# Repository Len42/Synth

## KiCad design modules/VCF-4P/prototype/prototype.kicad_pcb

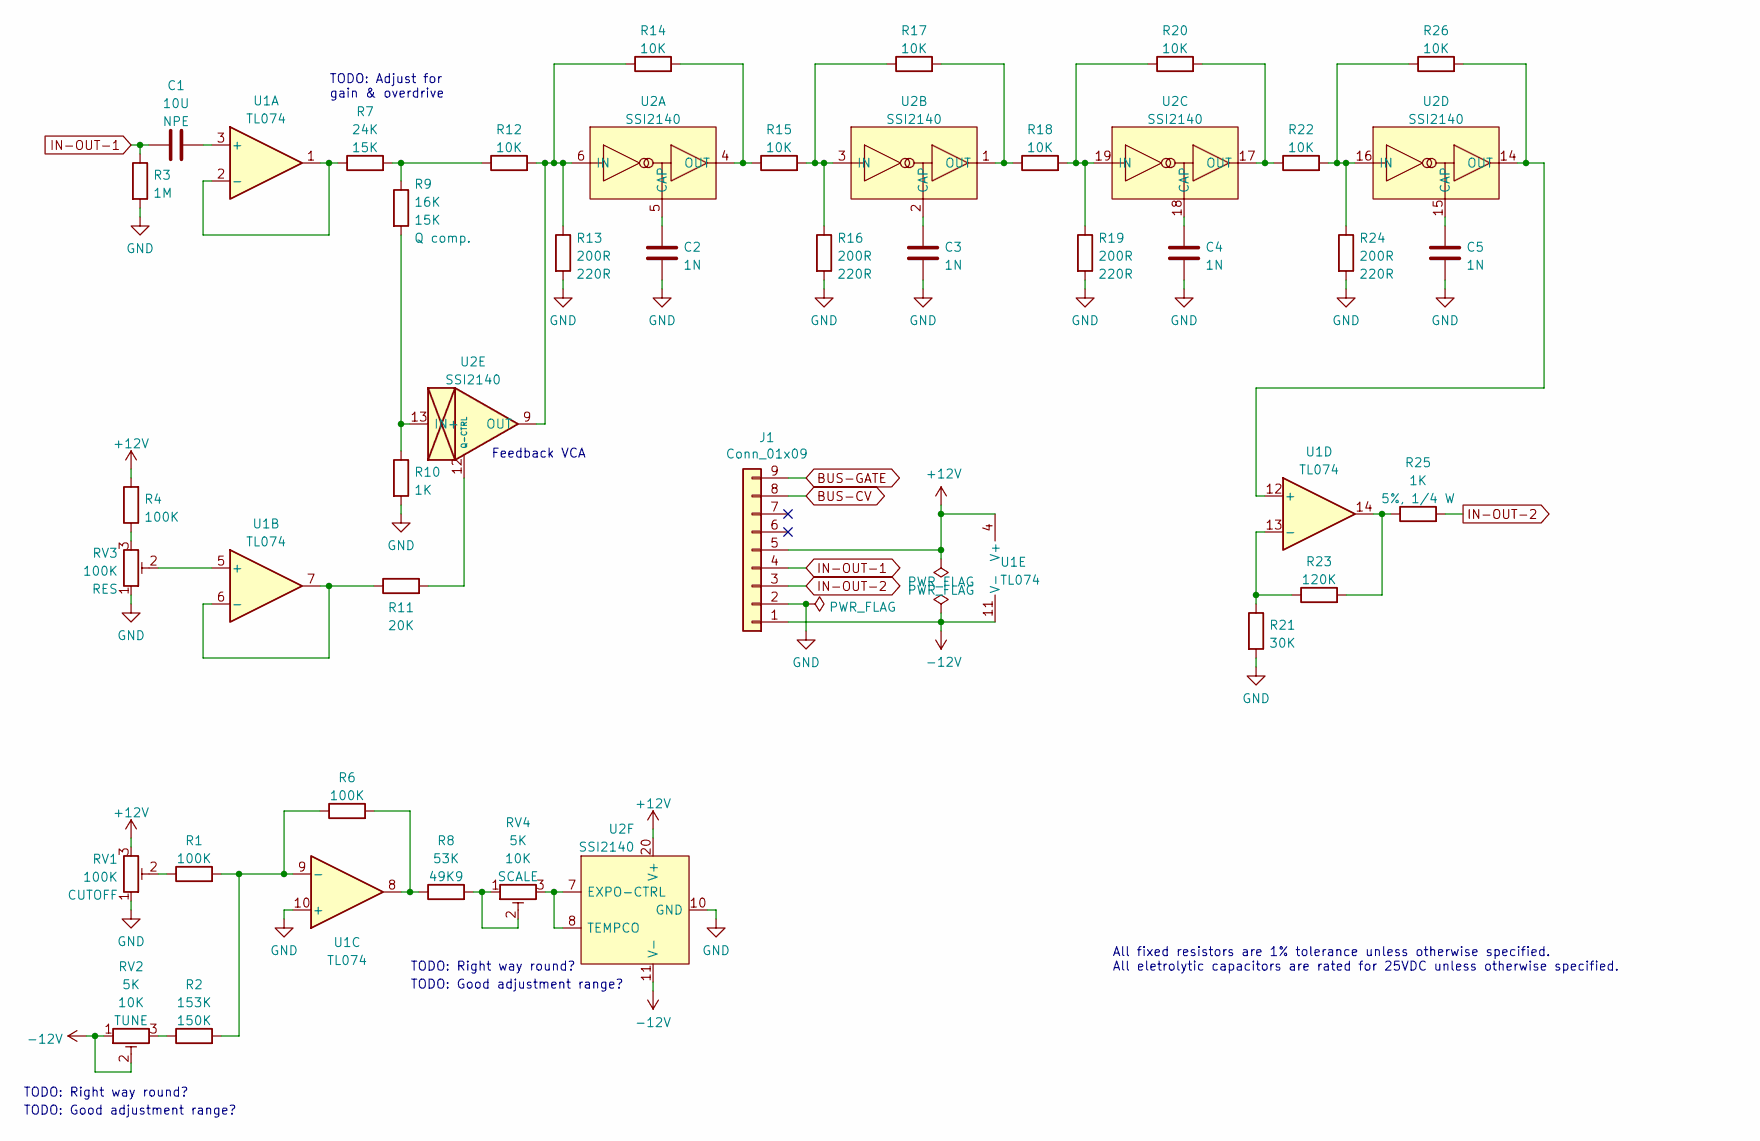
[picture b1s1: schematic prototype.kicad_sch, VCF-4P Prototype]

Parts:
C1: 10U; C_Radial_D5.0mm_H5.0mm_P2.50mm; ManufacturerPartNum ECE-A1EN100UI
C2, C3, C4, C5: 1N; C_Rect_Kemet_L7.2mm_W2.5mm_P5mm
J1: Conn_01x09; PinHeader_1x09_P2.54mm_Vertical
R1: 100K; R_Axial_DIN0207_L6.3mm_D2.5mm_P7.62mm_Horizontal; ManufacturerPartNum MFR-12*
R2: 153K; R_Axial_DIN0207_L6.3mm_D2.5mm_P7.62mm_Horizontal; ManufacturerPartNum MFR-12*
R3: 1M; SB_Gen_1; ManufacturerPartNum MFR-12*
R4: 100K; SB_Gen_2; ManufacturerPartNum MFR-12*
R6: 100K; SB_Gen_1; ManufacturerPartNum MFR-12*
R7: 24K; R_Axial_DIN0207_L6.3mm_D2.5mm_P7.62mm_Horizontal; ManufacturerPartNum MFR-12*
R8: 53K; R_Axial_DIN0207_L6.3mm_D2.5mm_P7.62mm_Horizontal; ManufacturerPartNum MFR-12*
R9: 16K; R_Axial_DIN0207_L6.3mm_D2.5mm_P7.62mm_Horizontal; ManufacturerPartNum MFR-12*
R10: 1K; SB_Gen_1; ManufacturerPartNum MFR-12*
R11: 20K; SB_Gen_1; ManufacturerPartNum MFR-12*
R12, R18: 10K; R_Axial_DIN0207_L6.3mm_D2.5mm_P7.62mm_Horizontal; ManufacturerPartNum MFR-12*
R13, R16, R19, R24: 200R; SB_Gen_1; ManufacturerPartNum MFR-12*
R14, R17, R20, R26: 10K; SB_Gen_2; ManufacturerPartNum MFR-12*
R15, R22: 10K; SB_Gen_1; ManufacturerPartNum MFR-12*
R21: 30K; R_Axial_DIN0207_L6.3mm_D2.5mm_P7.62mm_Horizontal; ManufacturerPartNum MFR-12*
R23: 120K; SB_Gen_1; ManufacturerPartNum MFR-12*
R25: 1K; SB_Gen_2; ManufacturerPartNum CCF071K00JKE36
RV1, RV3: 100K; Potentiometer_Bourns_3310R_Top; ManufacturerPartNum 3386*
RV2, RV4: 5K; Potentiometer_Bourns_3310R_Top; ManufacturerPartNum 3386*
U1: TL074; DIP-14_W7.62mm; ManufacturerPartNum TL074BCN
U2: SSI2140; Breakout_DIP-20_W15.24mm; ManufacturerPartNum SSI2140

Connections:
+12V: J1.5, R4.2, RV1.3, U1.4 (V+), U2.20 (V+)
-12V: J1.1, RV2.1, RV2.2, U1.11 (V-), U2.11 (V-)
BUS-CV: J1.8
BUS-GATE: J1.9
GND: C2.2, C3.2, C4.2, C5.2, J1.2, R3.2, R10.2, R13.2, R16.2, R19.2, R21.2, R24.2, RV1.1, RV3.1, U1.10 (+), U2.10 (GND)
IN-OUT-1: C1.1, J1.4, R3.1
IN-OUT-2: J1.3, R25.2
unnamed: C1.2, U1.3 (+)
unnamed: C2.1, U2.5 (CAP)
unnamed: C3.1, U2.2 (CAP)
unnamed: C4.1, U2.18 (CAP)
unnamed: C5.1, U2.15 (CAP)
unnamed: R1.1, RV1.2
unnamed: R1.2, R2.2, R6.1, U1.9 (-)
unnamed: R2.1, RV2.3
unnamed: R4.1, RV3.3
unnamed: R6.2, R8.1, U1.8
unnamed: R7.1, U1.1, U1.2 (-)
unnamed: R8.2, RV4.1, RV4.2
unnamed: R9.2, R10.1, U2.13 (IN+)
unnamed: R11.1, U1.6 (-), U1.7
unnamed: R11.2, U2.12 (Q-CTRL)
unnamed: R7.2, R9.1, R12.1
unnamed: R12.2, R13.1, R14.1, U2.6 (IN), U2.9 (OUT)
unnamed: R14.2, R15.1, U2.4 (OUT)
unnamed: R15.2, R16.1, R17.1, U2.3 (IN)
unnamed: R17.2, R18.1, U2.1 (OUT)
unnamed: R18.2, R19.1, R20.1, U2.19 (IN)
unnamed: R20.2, R22.1, U2.17 (OUT)
unnamed: R21.1, R23.1, U1.13 (-)
unnamed: R22.2, R24.1, R26.1, U2.16 (IN)
unnamed: R23.2, R25.1, U1.14
unnamed: R26.2, U1.12 (+), U2.14 (OUT)
unnamed: RV3.2, U1.5 (+)
unnamed: RV4.3, U2.7 (EXPO-CTRL), U2.8 (TEMPCO)

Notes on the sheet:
TODO: Good adjustment range?
TODO: Right way round?
TODO: Adjust for gain & overdrive
All fixed resistors are 1% tolerance unless otherwise specified. All eletrolytic capacitors are rated for 25VDC unless otherwise specified.
Feedback VCA

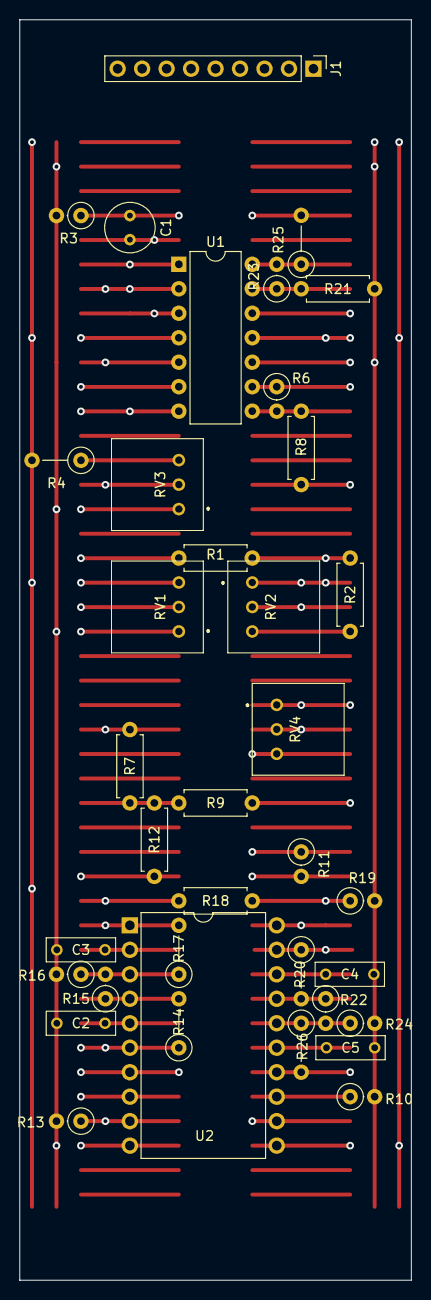
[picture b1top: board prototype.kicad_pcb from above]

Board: 6 copper layers, 40.6 x 130.8 mm, 37 parts (0 on the bottom side), 33 nets.

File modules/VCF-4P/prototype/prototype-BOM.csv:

Ref,Qty,Value,Value2,Note,Description,Datasheet,Manufacturer,ManuPartNum,Distributor1,DistributorPartNum1,DistributorPartLink1,Distributor2,DistributorPartNum2,DistributorPartLink2,Distributor3,DistributorPartNum3,DistributorPartLink3
"C1","1","10U","NPE","","Capacitor - Non-polarized Electrolytic","https://www.mouser.ca/datasheet/2/315/ABA0000C1053-947510.pdf","Panasonic","ECE-A1EN100UI","Mouser","667-ECE-A1EN100UI","https://www.mouser.ca/ProductDetail/Panasonic/ECE-A1EN100UI?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","","","","","",""
"C2 C3 C4 C5","4","1N","","","Capacitor - Film","","","","","","","","","","","",""
"J1","1","Conn_01x09","","","Generic connector, single row, 01x09, script generated (kicad-library-utils/schlib/autogen/connector/)","","","","","","","","","","","",""
"R1 R21","2","120K","1%, 1/6 W","","Resistor","https://www.mouser.ca/datasheet/2/447/Yageo_LR_MFR_1-1714151.pdf","YAGEO","MFR-12*","Mouser","603-MFR-12*","https://www.mouser.ca/c/?m=YAGEO&power+rating=166+mW+(1%2f6+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","","","","","",""
"R2","1","153K","150K","","Resistor","https://www.mouser.ca/datasheet/2/447/Yageo_LR_MFR_1-1714151.pdf","YAGEO","MFR-12*","Mouser","603-MFR-12*","https://www.mouser.ca/c/?m=YAGEO&power+rating=166+mW+(1%2f6+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","","","","","",""
"R3","1","1M","1%, 1/6 W","","Resistor","https://www.mouser.ca/datasheet/2/447/Yageo_LR_MFR_1-1714151.pdf","YAGEO","MFR-12*","Mouser","603-MFR-12*","https://www.mouser.ca/c/?m=YAGEO&power+rating=166+mW+(1%2f6+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","","","","","",""
"R4 R5 R6","3","100K","1%, 1/6 W","","Resistor","https://www.mouser.ca/datasheet/2/447/Yageo_LR_MFR_1-1714151.pdf","YAGEO","MFR-12*","Mouser","603-MFR-12*","https://www.mouser.ca/c/?m=YAGEO&power+rating=166+mW+(1%2f6+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","","","","","",""
"R7","1","24K","15K","","Resistor","https://www.mouser.ca/datasheet/2/447/Yageo_LR_MFR_1-1714151.pdf","YAGEO","MFR-12*","Mouser","603-MFR-12*","https://www.mouser.ca/c/?m=YAGEO&power+rating=166+mW+(1%2f6+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","","","","","",""
"R8","1","53K","49K9","","Resistor","https://www.mouser.ca/datasheet/2/447/Yageo_LR_MFR_1-1714151.pdf","YAGEO","MFR-12*","Mouser","603-MFR-12*","https://www.mouser.ca/c/?m=YAGEO&power+rating=166+mW+(1%2f6+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","","","","","",""
"R9","1","16K","15K","Q comp.","Resistor","https://www.mouser.ca/datasheet/2/447/Yageo_LR_MFR_1-1714151.pdf","YAGEO","MFR-12*","Mouser","603-MFR-12*","https://www.mouser.ca/c/?m=YAGEO&power+rating=166+mW+(1%2f6+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","","","","","",""
"R10","1","1K","1%, 1/6 W","","Resistor","https://www.mouser.ca/datasheet/2/447/Yageo_LR_MFR_1-1714151.pdf","YAGEO","MFR-12*","Mouser","603-MFR-12*","https://www.mouser.ca/c/?m=YAGEO&power+rating=166+mW+(1%2f6+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","","","","","",""
"R11","1","20K","1%, 1/6 W","","Resistor","https://www.mouser.ca/datasheet/2/447/Yageo_LR_MFR_1-1714151.pdf","YAGEO","MFR-12*","Mouser","603-MFR-12*","https://www.mouser.ca/c/?m=YAGEO&power+rating=166+mW+(1%2f6+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","","","","","",""
"R12 R14 R15 R17 R18 R20 R22 R26","8","10K","1%, 1/6 W","","Resistor","https://www.mouser.ca/datasheet/2/447/Yageo_LR_MFR_1-1714151.pdf","YAGEO","MFR-12*","Mouser","603-MFR-12*","https://www.mouser.ca/c/?m=YAGEO&power+rating=166+mW+(1%2f6+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","","","","","",""
"R13 R16 R19 R24","4","200R","220R","","Resistor","https://www.mouser.ca/datasheet/2/447/Yageo_LR_MFR_1-1714151.pdf","YAGEO","MFR-12*","Mouser","603-MFR-12*","https://www.mouser.ca/c/?m=YAGEO&power+rating=166+mW+(1%2f6+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","","","","","",""
"R23","1","30K","1%, 1/6 W","","Resistor","https://www.mouser.ca/datasheet/2/447/Yageo_LR_MFR_1-1714151.pdf","YAGEO","MFR-12*","Mouser","603-MFR-12*","https://www.mouser.ca/c/?m=YAGEO&power+rating=166+mW+(1%2f6+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","","","","","",""
"R25","1","1K","5%, 1/4 W","Output limiting","Resistor","https://www.mouser.ca/datasheet/2/427/ccf07-1762725.pdf","Vishay / Dale","CCF071K00JKE36","Mouser","71-CCF071K00JKE36","https://www.mouser.ca/ProductDetail/Vishay-Dale/CCF071K00JKE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","","","","","",""
"RV1 RV3","2","100K","","","Trim-potentiometer","https://www.mouser.ca/datasheet/2/54/3386-776606.pdf","Bourns","3386*","Mouser","652-3386*","https://www.mouser.ca/c/passive-components/resistors/variabl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","","","","","",""
"RV2 RV4","2","5K","10K","","Trim-potentiometer","https://www.mouser.ca/datasheet/2/54/3386-776606.pdf","Bourns","3386*","Mouser","652-3386*","https://www.mouser.ca/c/passive-components/resistors/variabl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","","","","","",""
"U1","1","TL074","","","Quad Low-Noise JFET-Input Operational Amplifiers, DIP-14/SOIC-14","http://www.ti.com/lit/ds/symlink/tl071.pdf","Texas Instruments","TL074BCN","Mouser","595-TL074BCN","https://www.mouser.ca/ProductDetail/?qs=vxEfx8VrU7BHurOY5iQd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","","","","","",""
"U2","1","SSI2140","","","Voltage Controlled Filter (VCF), SSOP-20","http://soundsemiconductor.com/downloads/ssi2140datasheet.pdf","Sound Semiconductor","SSI2140","Antique Electronic Supply","P-Q-SSI2140","https://www.tubesandmore.com/products/integrated-circuit-ssi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","SynthCube","ICSMSSI2140","https://synthcube.com/cart/ics-and-semiconductors/sound-semi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","Thonk","SSI2140","https://www.thonk.co.uk/shop/sound-semiconductor/"

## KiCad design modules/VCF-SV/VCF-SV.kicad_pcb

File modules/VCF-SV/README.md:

# State-Variable VCF

## 10HP Eurorack Module

_A state-variable filter using the CEM3320 chip_

### Features
- Two-pole state-variable filter made with a [CEM3320 IC](https://electricdruid.net/wp-content/uploads/2017/06/CEM3320-VCF.pdf)
- Two separate outputs:
    - Continuously-variable low-pass - notch - high-pass filter response
    - Bandpass filter
- Self-oscillates at maximum resonance
- Two CV inputs for cutoff/centre frequency. One is 1V/octave and the other has an input attenuator.
- 1V/octave input can default to the Eurorack bus CV line (jumper-selectable) - more info [here](https://lenp.net/synth/eurorack-bus-cv-gate.html)
- Resonance CV input with attenuator

### Notes
The cutoff CV inputs can be trimmed to track 1V/octave pretty well (but not as accurately as a VCO). The temperature-compensation resistor, RT1, should be mounted in thermal contact with the CEM3320 chip (see photo).

This module requires a 16-pin Eurorack power cable, but it does not depend on +5V power from the Eurorack system.

### Calibration
There are three trimmer potentiometers on the back of the module that should be adjusted for best results.

First, adjust the "DC TRIM" trimmer (RV8) to minimize control voltage feedthrough.
- Disconnect all inputs from the module.
- Set the cutoff and resonance controls fully counter-clockwise.
- Connect an audio signal (e.g. from a VCO) to the module's volt-per-octave CV input.
- Connect either of the the module's outputsj to an oscilloscope, or just listen to it.
- Adjust RV8 for the minimum output signal.

Then adjust RV6 (TUNE) and RV7 (SCALE) so the cutoff/centre frequency responds accurately to the volt-per-octave CV input. If you care.
- Disconnect the module's audio input.
- Connect a keyboard or other pitch CV source to the module's the 1V/octave CV input.
- Turn the resonance control fully clockwise. This will cause the filter to oscillate.
- Connect either of the the module's outputs to a tuner or frequency counter.
- Adjust RV6 & RV7 while playing different notes until the output is in tune (more or less) across several octaves.

Don't expect the tuning to be as accurate or as stable as a VCO.

If you don't care about precise volt/octave scaling, you can just set the trim pots RV6 & RV7 somewhere near the middle, or even replace them with fixed resistors (13 kΩ and 4.7 kΩ respectively). Also, you may replace tempco resistor RT1 with an ordinary resistor (1% metal film preferred).

### PCBs
PCB layouts are provided in KiCad and gerber formats. A PCB layout for a drilled front panel (with no labels) is also included.

The PCBs that I used can be ordered from OSH Park. The designs are here:
- [Front panel](https://oshpark.com/shared_projects/KgoN3yfz)
- [Controls board](https://oshpark.com/shared_projects/U095EDGt)
- [Main board](https://oshpark.com/shared_projects/O1sdHBEZ)

Please note that I am a hobbyist, not a trained electronics engineer. No guarantees!

### Acknowledgements

This design is based in part on the [Tellun TLN-428 module by Scott Juskiw](http://www.tellun.com/motm/diy/tln428/TLN-428.html).

### Software Used

* [KiCad](https://www.kicad.org/) 6.0.9

<hr /><div><div style="float:left; padding-right:10px;"></div><div style="xfloat:left; padding-left:10px;"><br />© 2022 Len Popp CC BY<br />This work is licensed under a <a rel="license" href="http://creativecommons.org/licenses/by/4.0/">Creative Commons Attribution 4.0 International License</a>.</div></div>

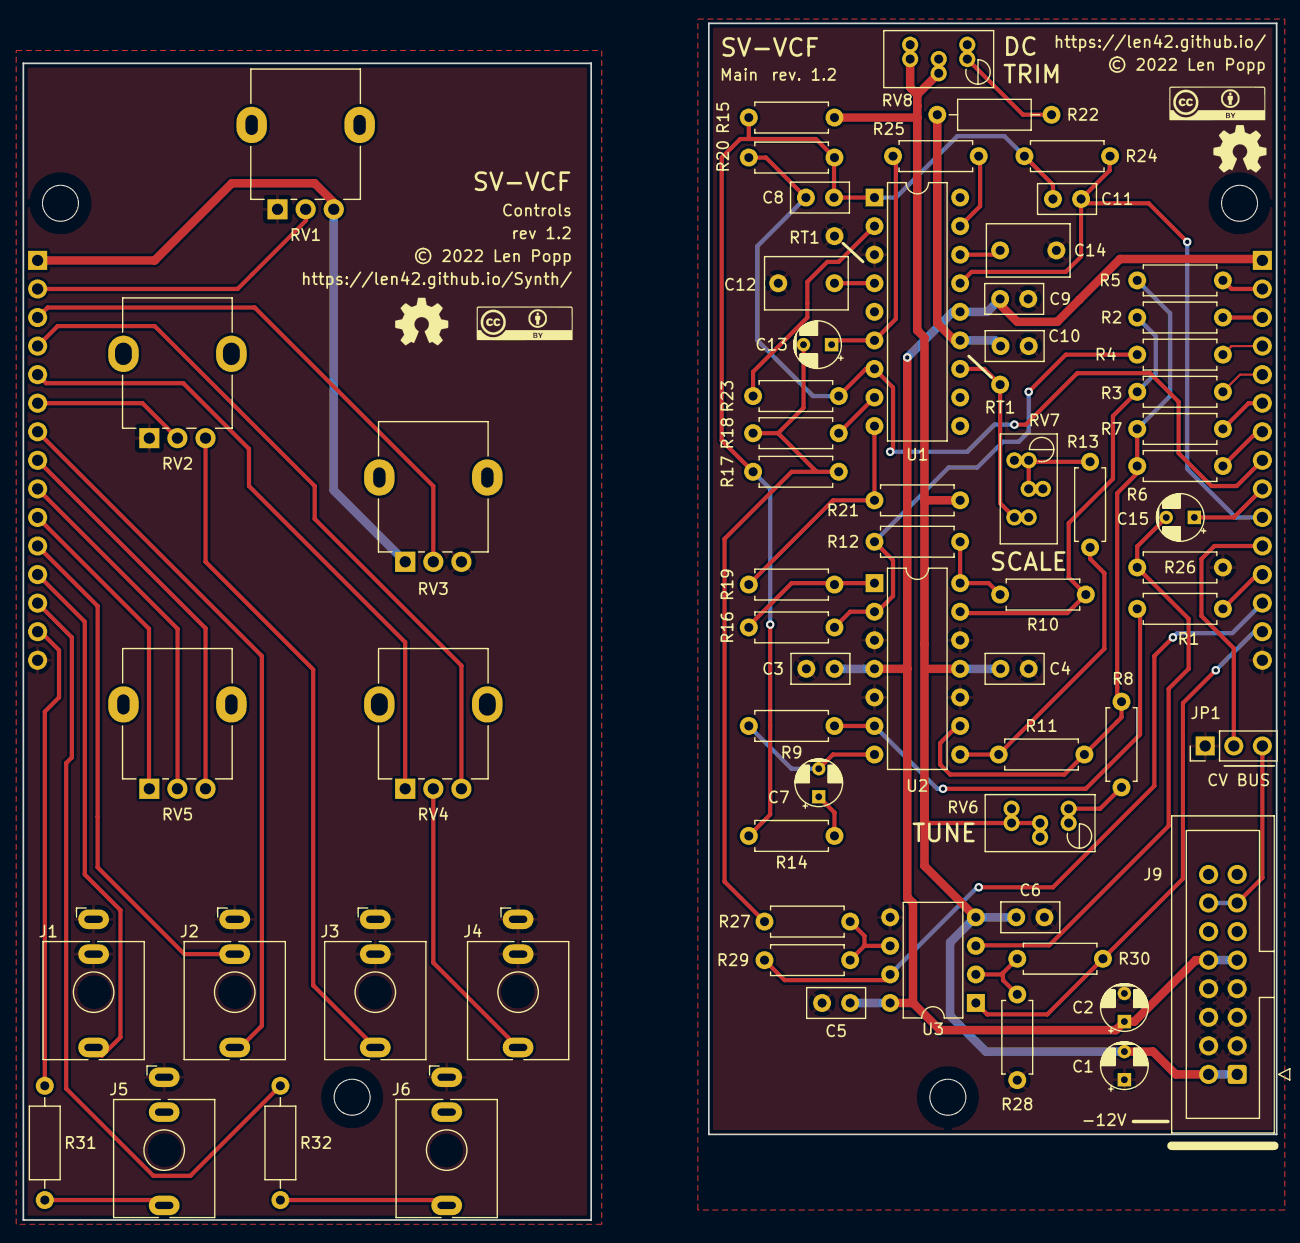
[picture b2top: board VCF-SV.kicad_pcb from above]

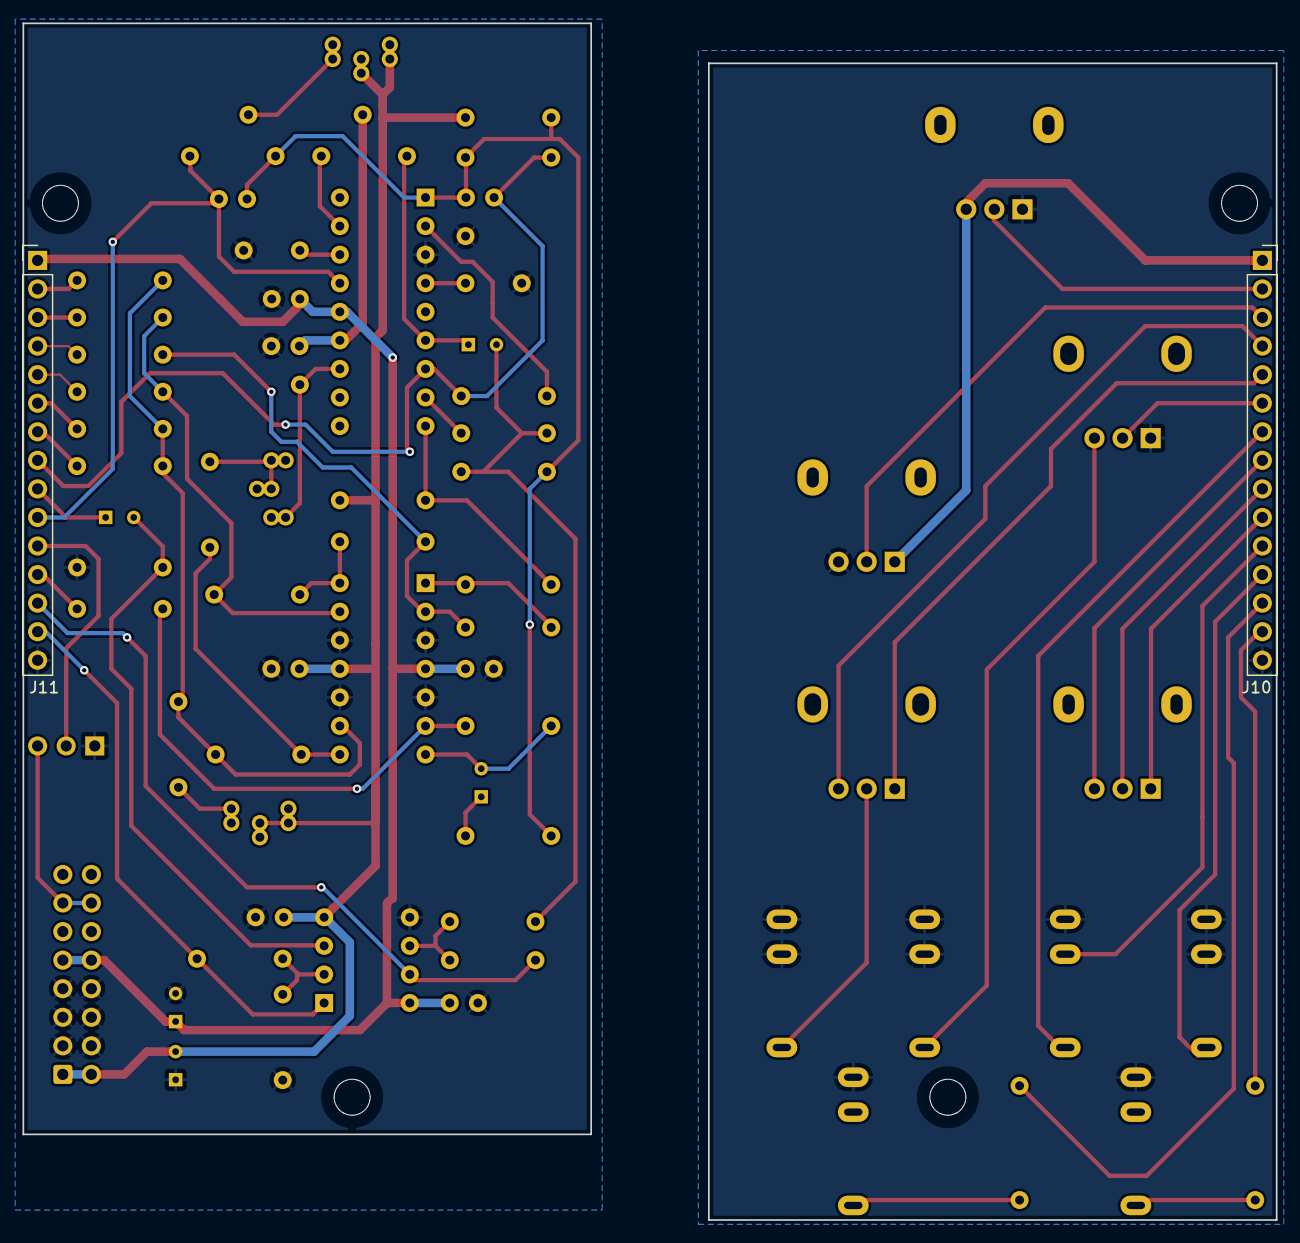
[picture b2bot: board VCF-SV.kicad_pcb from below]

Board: 2 copper layers, 50.5 x 98.8 mm, 78 parts (2 on the bottom side), 47 nets.

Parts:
C1, C2: 10U; CP_Radial_D4.0mm_P2.50mm
C3, C4, C5, C6, C9, C10: 100N; C_Disc_D5.0mm_W2.5mm_P2.50mm
C7, C13, C15: 4U7; CP_Radial_D4.0mm_P2.50mm
C8: 10P; C_Disc_D5.0mm_W2.5mm_P2.50mm
C11: 18P; C_Disc_D5.0mm_W2.5mm_P2.50mm
C12, C14: 150P; C_Rect_L7.2mm_W4.5mm_P5.00mm
G1, G2: Logo_CC_BY
G3, G4: Logo_OSHW
H1, H2, H3, H4: MountingHole_M3; MountingHole_PCB_3.2mm_M3
H12, H13: WireHole_PTH; WireHole_D0.8mm_OD1.6mm
J1, J2, J3, J4, J5, J6: WQP-PJ398; Jack_3.5mm_QingPu_WQP-PJ398SM_Vertical
J9: Conn_Eurorack_16; IDC-Header-Eurorack-16-TH
J10: Conn_Front_Left_Top; PinSocket_1x15_P2.54mm_Vertical
J11: Conn_Back_Right_Top; PinHeader_1x15_P2.54mm_Vertical
JP1: CV-BUS; PinHeader_1x03_P2.54mm_Vertical
R1: 200K; R_Axial_DIN0207_L6.3mm_D2.5mm_P7.62mm_Horizontal
R2: 130K; R_Axial_DIN0207_L6.3mm_D2.5mm_P7.62mm_Horizontal
R3, R4, R6, R7, R9, R10, R11, R12, R16, R19, R20, R23, R25, R28, R29, R30: 100K; R_Axial_DIN0207_L6.3mm_D2.5mm_P7.62mm_Horizontal
R5: 120K; R_Axial_DIN0207_L6.3mm_D2.5mm_P7.62mm_Horizontal
R8, R27: 68K; R_Axial_DIN0207_L6.3mm_D2.5mm_P7.62mm_Horizontal
R13: 47K; R_Axial_DIN0207_L6.3mm_D2.5mm_P7.62mm_Horizontal
R14, R24: 91K; R_Axial_DIN0207_L6.3mm_D2.5mm_P7.62mm_Horizontal
R15: 300K; R_Axial_DIN0207_L6.3mm_D2.5mm_P7.62mm_Horizontal
R17: 240K; R_Axial_DIN0207_L6.3mm_D2.5mm_P7.62mm_Horizontal
R18: 220K; R_Axial_DIN0207_L6.3mm_D2.5mm_P7.62mm_Horizontal
R21: 2M61; R_Axial_DIN0207_L6.3mm_D2.5mm_P7.62mm_Horizontal
R22: 680R; R_Axial_DIN0207_L6.3mm_D2.5mm_P10.16mm_Horizontal
R26: 1M; R_Axial_DIN0207_L6.3mm_D2.5mm_P7.62mm_Horizontal
R31, R32: 1K; R_Axial_DIN0207_L6.3mm_D2.5mm_P10.16mm_Horizontal
RV1, RV3, RV5: 100K; Potentiometer_Alpha_RD901F-40-00D_Single_Vertical
RV2, RV4: 100K; Potentiometer_SongHuei_Single_Vertical
RV6: 25K; Potentiometer_Bourns_3296WY_Vertical
RV7: 10K; Potentiometer_Bourns_3296WY_Vertical
RV8: 2K; Potentiometer_Bourns_3296WY_Vertical
U1: CEM3320; DIP-18_W7.62mm
U2: TL074; DIP-14_W7.62mm
U3: TL072; DIP-8_W7.62mm

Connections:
+12V: C2.1, C3.1, C5.1, C9.1, J9.9 (+12V), J9.10, J10.1, J11.1, RV1.3, RV3.1, U1.14 (VCC), U2.4 (V+), U3.8 (V+)
-12V: C1.2, C4.2, C6.2, J9.1 (-12V), J9.2, R15.2, R21.2, RV6.2, RV6.3, RV8.2, RV8.3, U2.11 (V-), U3.4 (V-)
/OUT-BP: C13.2, R17.2, R18.1, R27.1
/VEE-U1: C10.2, R22.1, U1.13 (VEE)
CV-FREQ-1VOCT: J2.T, J10.7, J11.7, R6.2
CV-FREQ-MOD: J10.6, J11.6, R7.2, RV2.2
CV-FREQ-POT: J10.2, J11.2, R5.2, RV1.2
CV-RES-MOD-N: J10.4, J11.4, R4.1, RV4.3
CV-RES-MOD-P: J10.5, J11.5, R3.1, RV4.1
CV-RES-POT: J10.3, J11.3, R2.1, RV3.2
GND: C1.1, C2.2, C3.2, C4.1, C5.2, C6.1, C9.2, C10.1, C12.2, C14.2, H13.1, J1.S, J1.TN, J2.S, J3.S, J3.TN, J4.S, J4.TN, J5.S, J6.S, J9.3 (GND), J9.4, J9.5 (GND), J9.6, J9.7 (GND), J9.8, J10.15, J11.15, JP1.1 (A), R26.2, R28.1, RV1.1, RV2.1, RV3.3, U1.3 (GND), U2.3 (+), U2.5 (+), U2.10 (+), U2.12 (+), U3.5 (+)
IN-AUDIO: J1.T, J10.12, J11.12, R1.1
IN-CV-BUS: J2.TN, J10.11, J11.11, JP1.2 (C)
unnamed: C7.1, R14.1
unnamed: C7.2, R9.2, U2.7
unnamed: C8.1, C11.1, R14.2, R15.1, R17.1, R20.1, R24.1, U1.1 (IN)
unnamed: C12.1, U1.4 (CAP)
unnamed: C13.1, R25.1, U1.6 (OUT)
unnamed: C14.1, U1.16 (CAP)
unnamed: C15.2, R26.1, U3.3 (+)
unnamed: H12.1, RV7.3, U1.12 (FREQ-CTRL)
unnamed: J3.T, RV2.3
unnamed: J4.T, RV4.2
unnamed: J5.T, R31.1
unnamed: J6.T, R32.1
unnamed: J9.13 (CV), J9.14, JP1.3 (B)
unnamed: R1.2, R9.1, U2.6 (-)
unnamed: R8.1, RV6.1
unnamed: R2.2, R3.2, R10.1, U2.13 (-)
unnamed: R10.2, R12.1, U2.14
unnamed: R5.1, R6.1, R7.1, R8.2, R11.1, U2.9 (-)
unnamed: R11.2, R13.1, U2.8
unnamed: R4.2, R12.2, R16.1, U2.2 (-)
unnamed: R13.2, RV7.1, RV7.2
unnamed: R16.2, R19.1, U2.1
unnamed: R18.2, U1.8 (FB)
unnamed: R19.2, R21.1, U1.9 (Q-CTRL)
unnamed: R22.2, RV8.1
unnamed: R23.2, U1.2 (IN)
unnamed: R25.2, U1.17 (IN)
unnamed: R27.2, R29.1, U3.6 (-)
unnamed: R28.2, R30.1, U3.2 (-)
OUT-AUDIO-BP: J10.13, J11.13, R29.2, R32.2, U3.7
OUT-AUDIO-LP-HP: J10.14, J11.14, R30.2, R31.2, U3.1
OUT-HP: C8.2, J10.8, J11.8, R20.2, R23.1, RV5.3, U1.7 (OUT)
OUT-LP: C11.2, J10.10, J11.10, R24.2, RV5.1, U1.15 (OUT)
OUT-LP-HP: C15.1, J10.9, J11.9, RV5.2

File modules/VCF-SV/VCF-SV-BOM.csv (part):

Ref,Qty,Value,Value2,Note,Description,Datasheet,Manufacturer,ManuPartNum,Distributor1,DistributorPartNum1,DistributorPartLink1,Distributor2,DistributorPartNum2,DistributorPartLink2,Distributor3,DistributorPartNum3,DistributorPartLink3
"A1","1","Cable_Eurorack_16","","Length as required","Eurorack 16-16 pin power & bus cable","","","","Thonk","","https://www.thonk.co.uk/shop/eurorack-power-cables/","SynthCube","","https://synthcube.com/cart/eurorack-ribbon-power-cables","Modular Addict","","https://modularaddict.com/parts/eurorack-power-cables-1"
"C1 C2","2","10U","35 VDC","12 V decoupling","Capacitor - Electrolytic - 12 V decoupling","https://www.mouser.ca/datasheet/2/315/ABA0000C1059-947582.pdf","Panasonic","ECE-A1VKS100I","Mouser","667-ECE-A1VKS100I","https://www.mouser.ca/ProductDetail/667-ECE-A1VKS100I","Thonk","Group_Eurorack_DIY_Essential","https://www.thonk.co.uk/shop/eurorack-diy-essentials/","","",""
"C3 C4 C5 C6 C9 C10","6","100N","","IC decoupling","Capacitor - Ceramic - IC decoupling","https://product.tdk.com/system/files/dam/doc/product/capacit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","TDK","FG18X7R1H104KNT06","Mouser","810-FG18X7R1H104KNT6","https://www.mouser.ca/ProductDetail/810-FG18X7R1H104KNT6","","","","","",""
"C7 C13 C15","3","4U7","","","Capacitor - Electrolytic","https://www.mouser.ca/datasheet/2/315/ABA0000C1050-947578.pdf","Panasonic","ECE-A1HKA4R7I","Mouser","667-ECE-A1HKA4R7I","https://www.mouser.ca/ProductDetail/Panasonic/ECE-A1HKA4R7I?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","","","","","",""
"C8","1","10P","C0G/NP0","","Capacitor - Ceramic","https://product.tdk.com/system/files/dam/doc/product/capacit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","TDK","FG18C0G1H100DNT00","Mouser","810-FG18C0G1H100DNT0","https://www.mouser.ca/ProductDetail/TDK/FG18C0G1H100DNT00?qs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","","","","","",""
"C11","1","18P","C0G/NP0","","Capacitor - Ceramic","https://www.mouser.ca/datasheet/2/427/kseries-1763315.pdf","Murata","K180J15C0GF5TL2","Mouser","594-K180J15C0GF5TL2","https://www.mouser.ca/ProductDetail/?qs=s%2FCsB4POEK6rPX34ea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","","","","","",""
"C12 C14","2","150P","","","Capacitor - Film","https://www.mouser.ca/datasheet/2/212/1/KEM_F3036_PFR-1102852.pdf","KEMET","PFR5151J63J11L4BULK","Mouser","80-PFR5151J63J11L4","https://www.mouser.ca/ProductDetail/KEMET/PFR5151J63J11L4BUL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","","","","","",""
"H5 H7 H8 H10","4","HW_Screw_M3x0.50x6","","","Machine screw, M3x0.50x6","","","","","","","","","","","",""
"H6 H9","2","HW_Standoff_F-F_11mm_M3x0.50","","","Standoff, 11mm, female-female, M3x0.50","https://www.thonk.co.uk/wp-content/uploads/2018/05/standoff-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","Ettinger","05.03.111","Thonk","Mech_11mm_Standoff_(x10)","https://www.thonk.co.uk/shop/standoffs/","Mouser","710-970110321","https://www.mouser.ca/ProductDetail/Wurth-Elektronik/9701103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","Mouser","144-MTS-11","https://www.mouser.ca/ProductDetail/144-MTS-11"
"H11","1","Jumper_2","","","Jumper connector, 2-pin socket","https://www.mouser.ca/datasheet/2/209/KC-301174-1171759.pdf","","","Mouser","151-8013-E","https://www.mouser.ca/ProductDetail/Kobiconn/151-8013-E?qs=R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","Adafruit","3525","https://www.adafruit.com/product/3525","","",""
"J1 J2 J3 J4 J5 J6","6","WQP-PJ398","","","Audio Jack, 2 Poles (Mono / TS), Switched T Pole (Normalling), QingPu / Thonkiconn","http://www.qingpu-electronics.com/en/products/WQP-PJ398SM-362.html","QingPu / Thonk","PJ398SM / WQP518MA","Thonk","PJ398SM","https://www.thonk.co.uk/shop/thonkiconn/","SynthCube","WQP518MA","https://synthcube.com/cart/3-5mm-euro-jacks","Adafruit","4031","https://www.adafruit.com/product/4031"
"J9","1","Conn_Eurorack_16","","","Eurorack 16-pin board power/CV/gate bus connector","https://www.mouser.ca/datasheet/2/445/61201621621-1717735.pdf","Wurth Elektronik","61201621621","Mouser","710-61201621621","https://www.mouser.ca/ProductDetail/Wurth-Elektronik/6120162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","","","","","",""
"J10","1","Conn_Front_Left_Top","","","Generic connector, single row, 01x15, script generated (kicad-library-utils/schlib/autogen/connector/)","","","","Adafruit","598","https://www.adafruit.com/product/598","Mouser","710-61303211821","https://www.mouser.ca/ProductDetail/Wurth-Elektronik/6130321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","","",""
"J11","1","Conn_Back_Right_Top","","","Generic connector, single row, 01x15, script generated (kicad-library-utils/schlib/autogen/connector/)","","","","Adafruit","392","https://www.adafruit.com/product/392","Mouser","649-1012937893601BLF","https://www.mouser.ca/ProductDetail/649-1012937893601BLF","","",""
"JP1","1","CV-BUS","","","Jumper pins, 3-pole, pins 1+2 closed/bridged","","","","Adafruit","392","https://www.adafruit.com/product/392","Mouser","649-1012937893601BLF","https://www.mouser.ca/ProductDetail/649-1012937893601BLF","","",""
"R1","1","200K","1%, 1/6 W","","Resistor","https://www.mouser.ca/datasheet/2/447/Yageo_LR_MFR_1-1714151.pdf","YAGEO","MFR-12FTF52-200K","Mouser"," 603-MFR-12FTF52-200K","https://www.mouser.ca/ProductDetail/YAGEO/MFR-12FTF52-200K?q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","","","","","",""
"R2","1","130K","1%, 1/6 W","","Resistor","https://www.mouser.ca/datasheet/2/447/Yageo_LR_MFR_1-1714151.pdf","YAGEO","MFR-12FTF52-130K","Mouser","603-MFR-12FTF52-130K","https://www.mouser.ca/ProductDetail/YAGEO/MFR-12FTF52-130K?q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","","","","","",""
"R3 R4 R6 R7 R9 R10 R11 R12 R16 R19 R20 R23 R25 R28 R29 R30","16","100K","1%, 1/6 W","","Resistor","https://www.mouser.ca/datasheet/2/447/Yageo_LR_MFR_1-1714151.pdf","YAGEO","MFR-12FTF52-100K","Mouser","603-MFR-12FTF52-100K","https://www.mouser.ca/ProductDetail/YAGEO/MFR-12FTF52-100K?q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","","","","","",""
"R5","1","120K","1%, 1/6 W","","Resistor","https://www.mouser.ca/datasheet/2/447/Yageo_LR_MFR_1-1714151.pdf","YAGEO","MFR-12FTF52-120K","Mouser","603-MFR-12FTF52-120K","https://www.mouser.ca/ProductDetail/YAGEO/MFR-12FTF52-120K?q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","","","","","",""
"R8 R27","2","68K","1%, 1/6 W","","Resistor","https://www.mouser.ca/datasheet/2/447/Yageo_LR_MFR_1-1714151.pdf","YAGEO","MFR-12FTF52-68K","Mouser","603-MFR-12FTF52-68K","https://www.mouser.ca/ProductDetail/YAGEO/MFR-12FTF52-68K?qs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","","","","","",""
"R13","1","47K","1%, 1/6 W","","Resistor","https://www.mouser.ca/datasheet/2/447/Yageo_LR_MFR_1-1714151.pdf","YAGEO","MFR-12FTF52-47K","Mouser","603-MFR-12FTF52-47K","https://www.mouser.ca/ProductDetail/YAGEO/MFR-12FTF52-47K?qs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","","","","","",""
"R14 R24","2","91K","1%, 1/6 W","","Resistor","https://www.mouser.ca/datasheet/2/447/Yageo_LR_MFR_1-1714151.pdf","YAGEO","MFR-12FTF52-91K","Mouser","603-MFR-12FTF52-91K","https://www.mouser.ca/ProductDetail/YAGEO/MFR-12FTF52-91K?qs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","","","","","",""
"R15","1","300K","1%, 1/6 W","","Resistor","https://www.mouser.ca/datasheet/2/447/Yageo_LR_MFR_1-1714151.pdf","YAGEO","MFR-25FRF52-300K","Mouser","603-MFR-25FRF52-300K","https://www.mouser.ca/ProductDetail/YAGEO/MFR-25FRF52-300K?q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","","","","","",""
"R17","1","240K","1%, 1/6 W","","Resistor","https://www.mouser.ca/datasheet/2/447/Yageo_LR_MFR_1-1714151.pdf","YAGEO","MFR-12FTF52-240K","Mouser","603-MFR-12FTF52-240K","https://www.mouser.ca/ProductDetail/YAGEO/MFR-12FTF52-240K?q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","","","","","",""
"R18","1","220K","1%, 1/6 W","","Resistor","https://www.mouser.ca/datasheet/2/447/Yageo_LR_MFR_1-1714151.pdf","YAGEO","MFR-12FTF52-220K","Mouser","603-MFR-12FTF52-220K","https://www.mouser.ca/ProductDetail/YAGEO/MFR-12FTF52-220K?q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","","","","","",""
"R21","1","2M61","1%, 1/6 W","","Resistor","https://www.mouser.ca/datasheet/2/447/Yageo_LR_MFR_1-1714151.pdf","YAGEO","MFR-25FTE52-2M61","Mouser","603-MFR-25FTE52-2M61","https://www.mouser.ca/ProductDetail/YAGEO/MFR-25FTE52-2M61?q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","","","","","",""
"R22","1","680R","1%, 1/6 W","","Resistor","https://www.mouser.ca/datasheet/2/447/Yageo_LR_MFR_1-1714151.pdf","YAGEO","MFR-12FTF52-680R","Mouser","603-MFR-12FTF52-680R","https://www.mouser.ca/ProductDetail/YAGEO/MFR-12FTF52-680R?q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","","","","","",""
"R26","1","1M","1%, 1/6 W","","Resistor","https://www.mouser.ca/datasheet/2/447/Yageo_LR_MFR_1-1714151.pdf","YAGEO","MFR-12FTE52-1M","Mouser","603-MFR-12FTE52-1M","https://www.mouser.ca/ProductDetail/YAGEO/MFR-12FTE52-1M?qs=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","","","","","",""
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
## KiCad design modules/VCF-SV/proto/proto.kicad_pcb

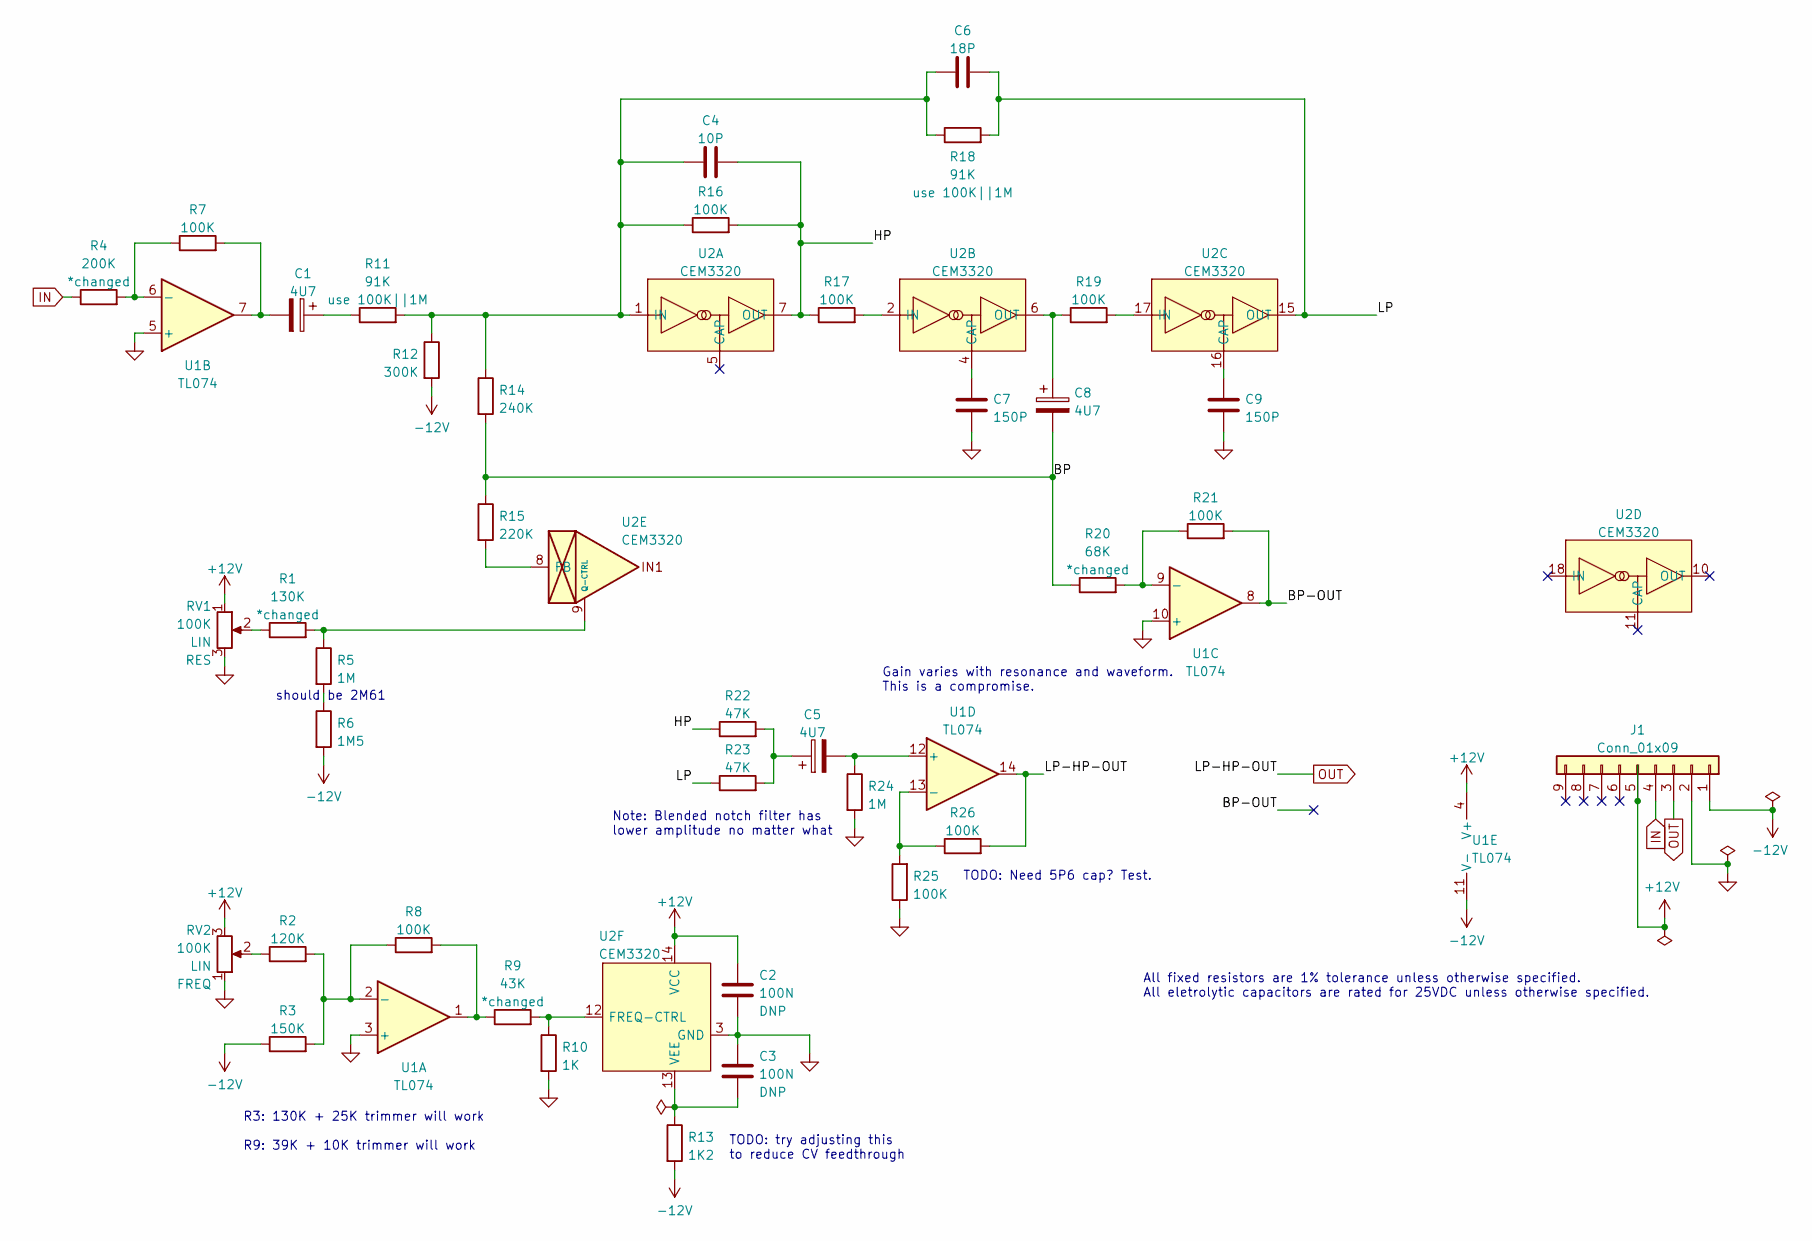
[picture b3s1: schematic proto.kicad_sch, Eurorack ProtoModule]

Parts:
C1, C5, C8: 4U7; CP_Radial_D4.0mm_P2.50mm
C2, C3: 100N; C_Disc_D5.0mm_W2.5mm_P2.50mm; ManufacturerPartNum FG18X7R1H104KNT06
C4: 10P; C_Disc_D5.0mm_W2.5mm_P2.50mm
C6: 18P; C_Disc_D5.0mm_W2.5mm_P2.50mm
C7, C9: 150P; C_Rect_L7.2mm_W4.5mm_P5.00mm
J1: Conn_01x09; PinHeader_1x09_P2.54mm_Vertical
R1: 130K; R_Axial_DIN0207_L6.3mm_D2.5mm_P7.62mm_Horizontal; ManufacturerPartNum MFR-12*
R2: 120K; SB_Gen_5; ManufacturerPartNum MFR-12*
R3: 150K; R_Axial_DIN0207_L6.3mm_D2.5mm_P7.62mm_Horizontal; ManufacturerPartNum MFR-12*
R4: 200K; R_Axial_DIN0207_L6.3mm_D2.5mm_P7.62mm_Horizontal; ManufacturerPartNum MFR-12*
R5, R24: 1M; SB_Gen_1; ManufacturerPartNum MFR-12*
R6: 1M5; R_Axial_DIN0207_L6.3mm_D2.5mm_P7.62mm_Horizontal; ManufacturerPartNum MFR-12*
R7, R8, R16, R21, R25, R26: 100K; SB_Gen_1; ManufacturerPartNum MFR-12*
R9: 43K; SB_Gen_1; ManufacturerPartNum MFR-12*
R10: 1K; SB_Gen_1; ManufacturerPartNum MFR-12*
R11: 91K; R_Axial_DIN0207_L6.3mm_D2.5mm_P7.62mm_Horizontal; ManufacturerPartNum MFR-12*
R12: 300K; SB_Gen_2; ManufacturerPartNum MFR-12*
R13: 1K2; SB_Gen_4; ManufacturerPartNum MFR-12*
R14: 240K; R_Axial_DIN0207_L6.3mm_D2.5mm_P7.62mm_Horizontal; ManufacturerPartNum MFR-12*
R15: 220K; R_Axial_DIN0207_L6.3mm_D2.5mm_P7.62mm_Horizontal; ManufacturerPartNum MFR-12*
R17: 100K; SB_Gen_5; ManufacturerPartNum MFR-12*
R18: 91K; SB_Gen_1; ManufacturerPartNum MFR-12*
R19: 100K; SB_Gen_2; ManufacturerPartNum MFR-12*
R20: 68K; R_Axial_DIN0207_L6.3mm_D2.5mm_P7.62mm_Horizontal; ManufacturerPartNum MFR-12*
R22, R23: 47K; SB_Gen_1; ManufacturerPartNum MFR-12*
RV1, RV2: 100K; Potentiometer_Bourns_3310R_Top
U1: TL074; DIP-14_W7.62mm; ManufacturerPartNum TL074BCN
U2: CEM3320; DIP-18_W7.62mm; ManufacturerPartNum 3320

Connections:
+12V: C2.1, J1.5, RV1.1, RV2.3, U1.4 (V+), U2.14 (VCC)
-12V: J1.1, R3.1, R6.2, R12.2, R13.2, U1.11 (V-)
/BP: C8.2, R14.2, R15.1, R20.1
/BP-OUT: R21.2, U1.8
/HP: C4.2, R16.2, R17.1, R22.1, U2.7 (OUT)
/LP: C6.2, R18.2, R23.1, U2.15 (OUT)
GND: C2.2, C3.1, C7.2, C9.2, J1.2, R10.2, R24.2, R25.1, RV1.3, RV2.1, U1.3 (+), U1.5 (+), U1.10 (+), U2.3 (GND)
IN: J1.4, R4.1
unnamed: C1.1, R11.1
unnamed: C1.2, R7.2, U1.7
unnamed: C3.2, R13.1, U2.13 (VEE)
unnamed: C4.1, C6.1, R11.2, R12.1, R14.1, R16.1, R18.1, U2.1 (IN)
unnamed: C5.1, R22.2, R23.2
unnamed: C5.2, R24.1, U1.12 (+)
unnamed: C7.1, U2.4 (CAP)
unnamed: C8.1, R19.1, U2.6 (OUT)
unnamed: C9.1, U2.16 (CAP)
unnamed: R1.1, RV1.2
unnamed: R1.2, R5.1, U2.9 (Q-CTRL)
unnamed: R2.1, RV2.2
unnamed: R2.2, R3.2, R8.1, U1.2 (-)
unnamed: R4.2, R7.1, U1.6 (-)
unnamed: R5.2, R6.1
unnamed: R8.2, R9.1, U1.1
unnamed: R9.2, R10.1, U2.12 (FREQ-CTRL)
unnamed: R15.2, U2.8 (FB)
unnamed: R17.2, U2.2 (IN)
unnamed: R19.2, U2.17 (IN)
unnamed: R20.2, R21.1, U1.9 (-)
unnamed: R25.2, R26.1, U1.13 (-)
OUT: J1.3, R26.2, U1.14

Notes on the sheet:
should be 2M61
Gain varies with resonance and waveform. This is a compromise.
TODO: try adjusting this to reduce CV feedthrough
TODO: Need 5P6 cap? Test.
All fixed resistors are 1% tolerance unless otherwise specified. All eletrolytic capacitors are rated for 25VDC unless otherwise specified.
Note: Blended notch filter has lower amplitude no matter what
R3: 130K + 25K trimmer will work R9: 39K + 10K trimmer will work

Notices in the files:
modules/VCF-4P/prototype-2p/prototype.kicad_sch:
Copyright © 2022 Len Popp CC BY
